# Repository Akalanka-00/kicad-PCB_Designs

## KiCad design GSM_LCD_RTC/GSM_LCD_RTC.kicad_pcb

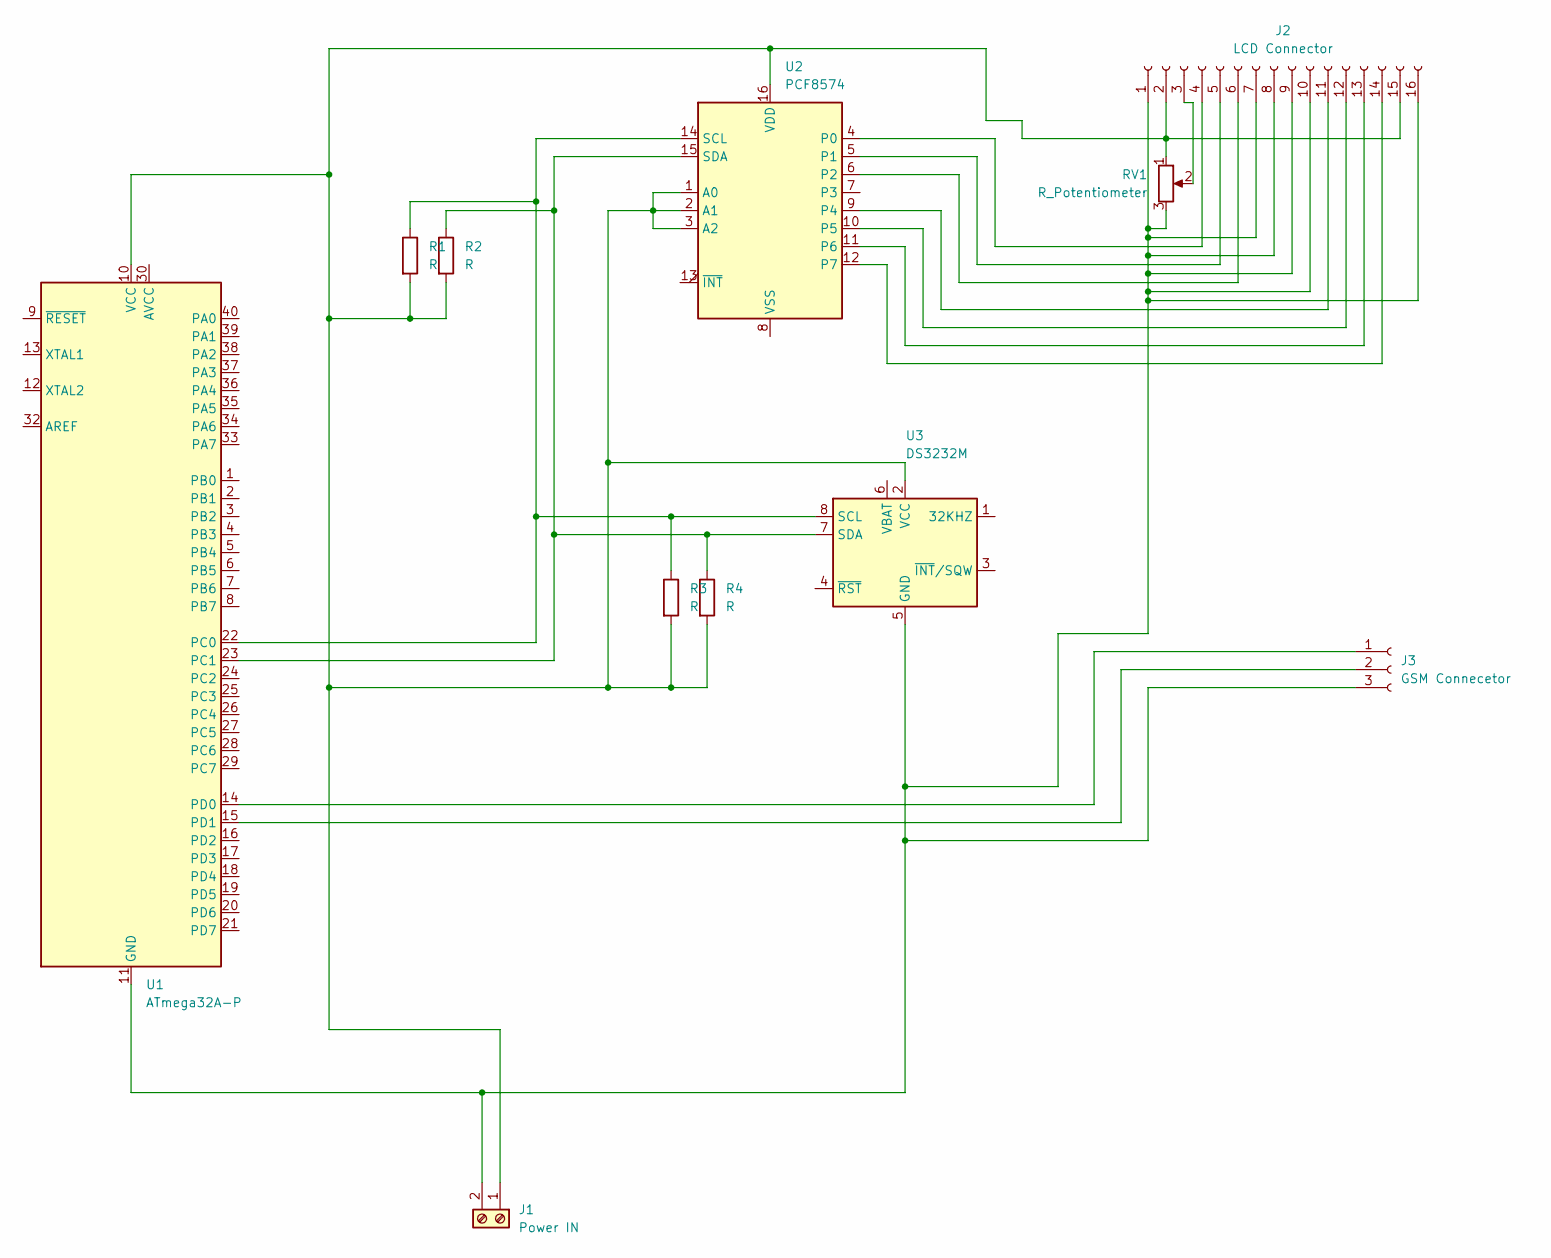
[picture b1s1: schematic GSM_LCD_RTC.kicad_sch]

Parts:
J1: Power IN; PhoenixContact_MSTBA_2,5_2-G_1x02_P5.00mm_Horizontal
J2: LCD Connector; PinHeader_1x16_P2.54mm_Vertical
J3: GSM Connecetor; PinSocket_1x03_P2.54mm_Vertical
R1, R2, R3, R4: R; R_Axial_DIN0411_L9.9mm_D3.6mm_P20.32mm_Horizontal
RV1: R_Potentiometer
U1: ATmega32A-P; DIP-40_W15.24mm
U2: PCF8574; Pololu_Breakout-16_15.2x20.3mm
U3: DS3232M; SOIC-8_3.9x4.9mm_P1.27mm

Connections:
unnamed: J1.1, J2.2, J2.15, R1.2, R2.2, R3.2, R4.2, RV1.1, U1.10 (VCC), U2.1 (A0), U2.2 (A1), U2.3 (A2), U2.16 (VDD), U3.2 (VCC)
unnamed: J1.2, J2.1, J2.7, J2.8, J2.9, J2.10, J2.16, J3.3, RV1.3, U1.11 (GND), U1.31 (GND), U3.5 (GND)
unnamed: J2.3, RV1.2
unnamed: J2.4, U2.4 (P0)
unnamed: J2.5, U2.5 (P1)
unnamed: J2.6, U2.6 (P2)
unnamed: J2.11, U2.9 (P4)
unnamed: J2.12, U2.10 (P5)
unnamed: J2.13, U2.11 (P6)
unnamed: J2.14, U2.12 (P7)
unnamed: J3.1, U1.14 (PD0)
unnamed: J3.2, U1.15 (PD1)
unnamed: R1.1, R3.1, U1.22 (PC0), U2.14 (SCL), U3.8 (SCL)
unnamed: R2.1, R4.1, U1.23 (PC1), U2.15 (SDA), U3.7 (SDA)

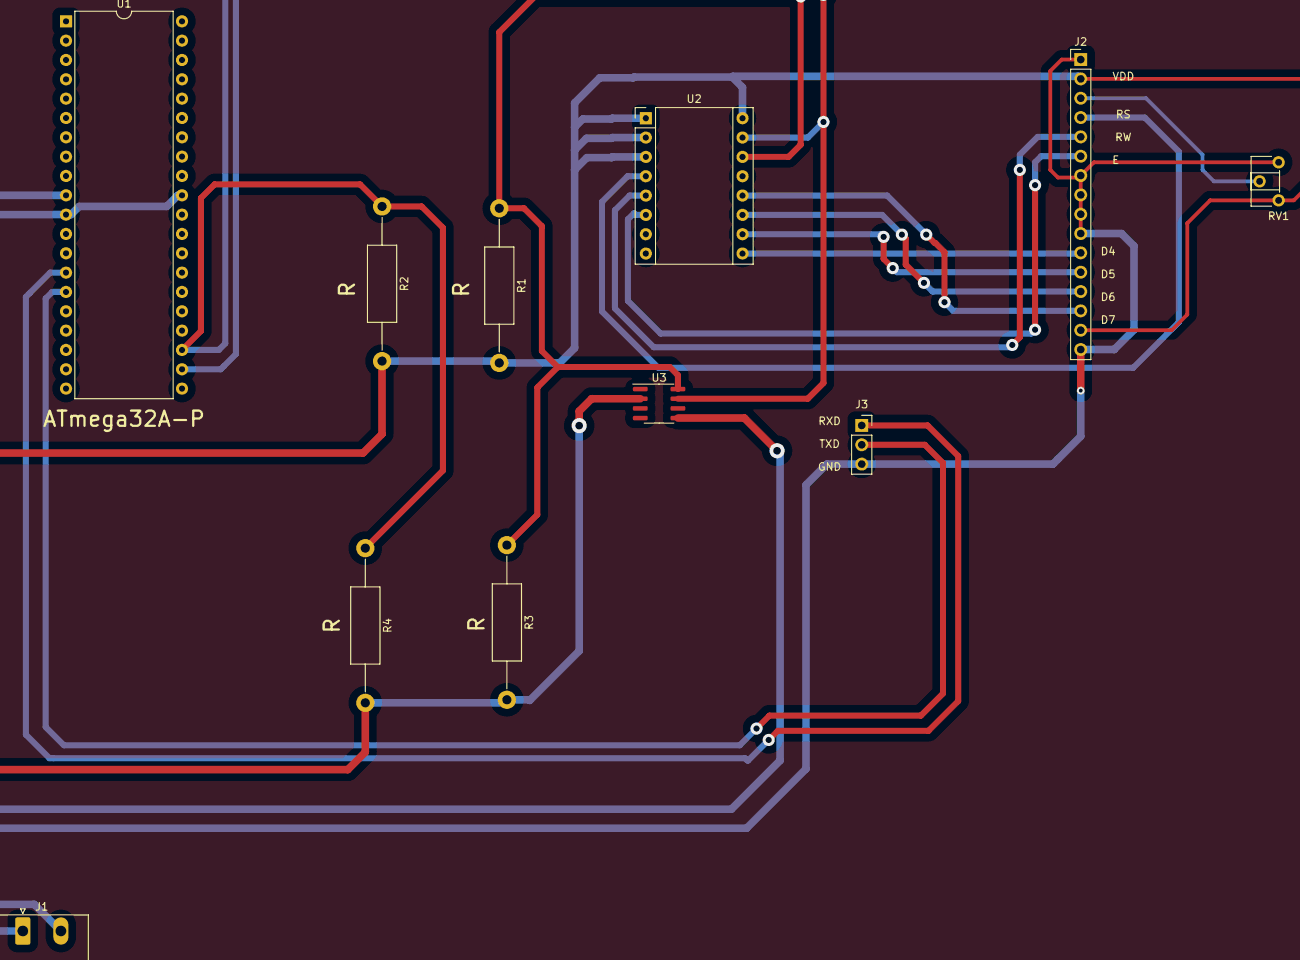
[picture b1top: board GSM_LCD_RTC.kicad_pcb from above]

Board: 2 copper layers, 11 parts (0 on the bottom side), 14 nets.

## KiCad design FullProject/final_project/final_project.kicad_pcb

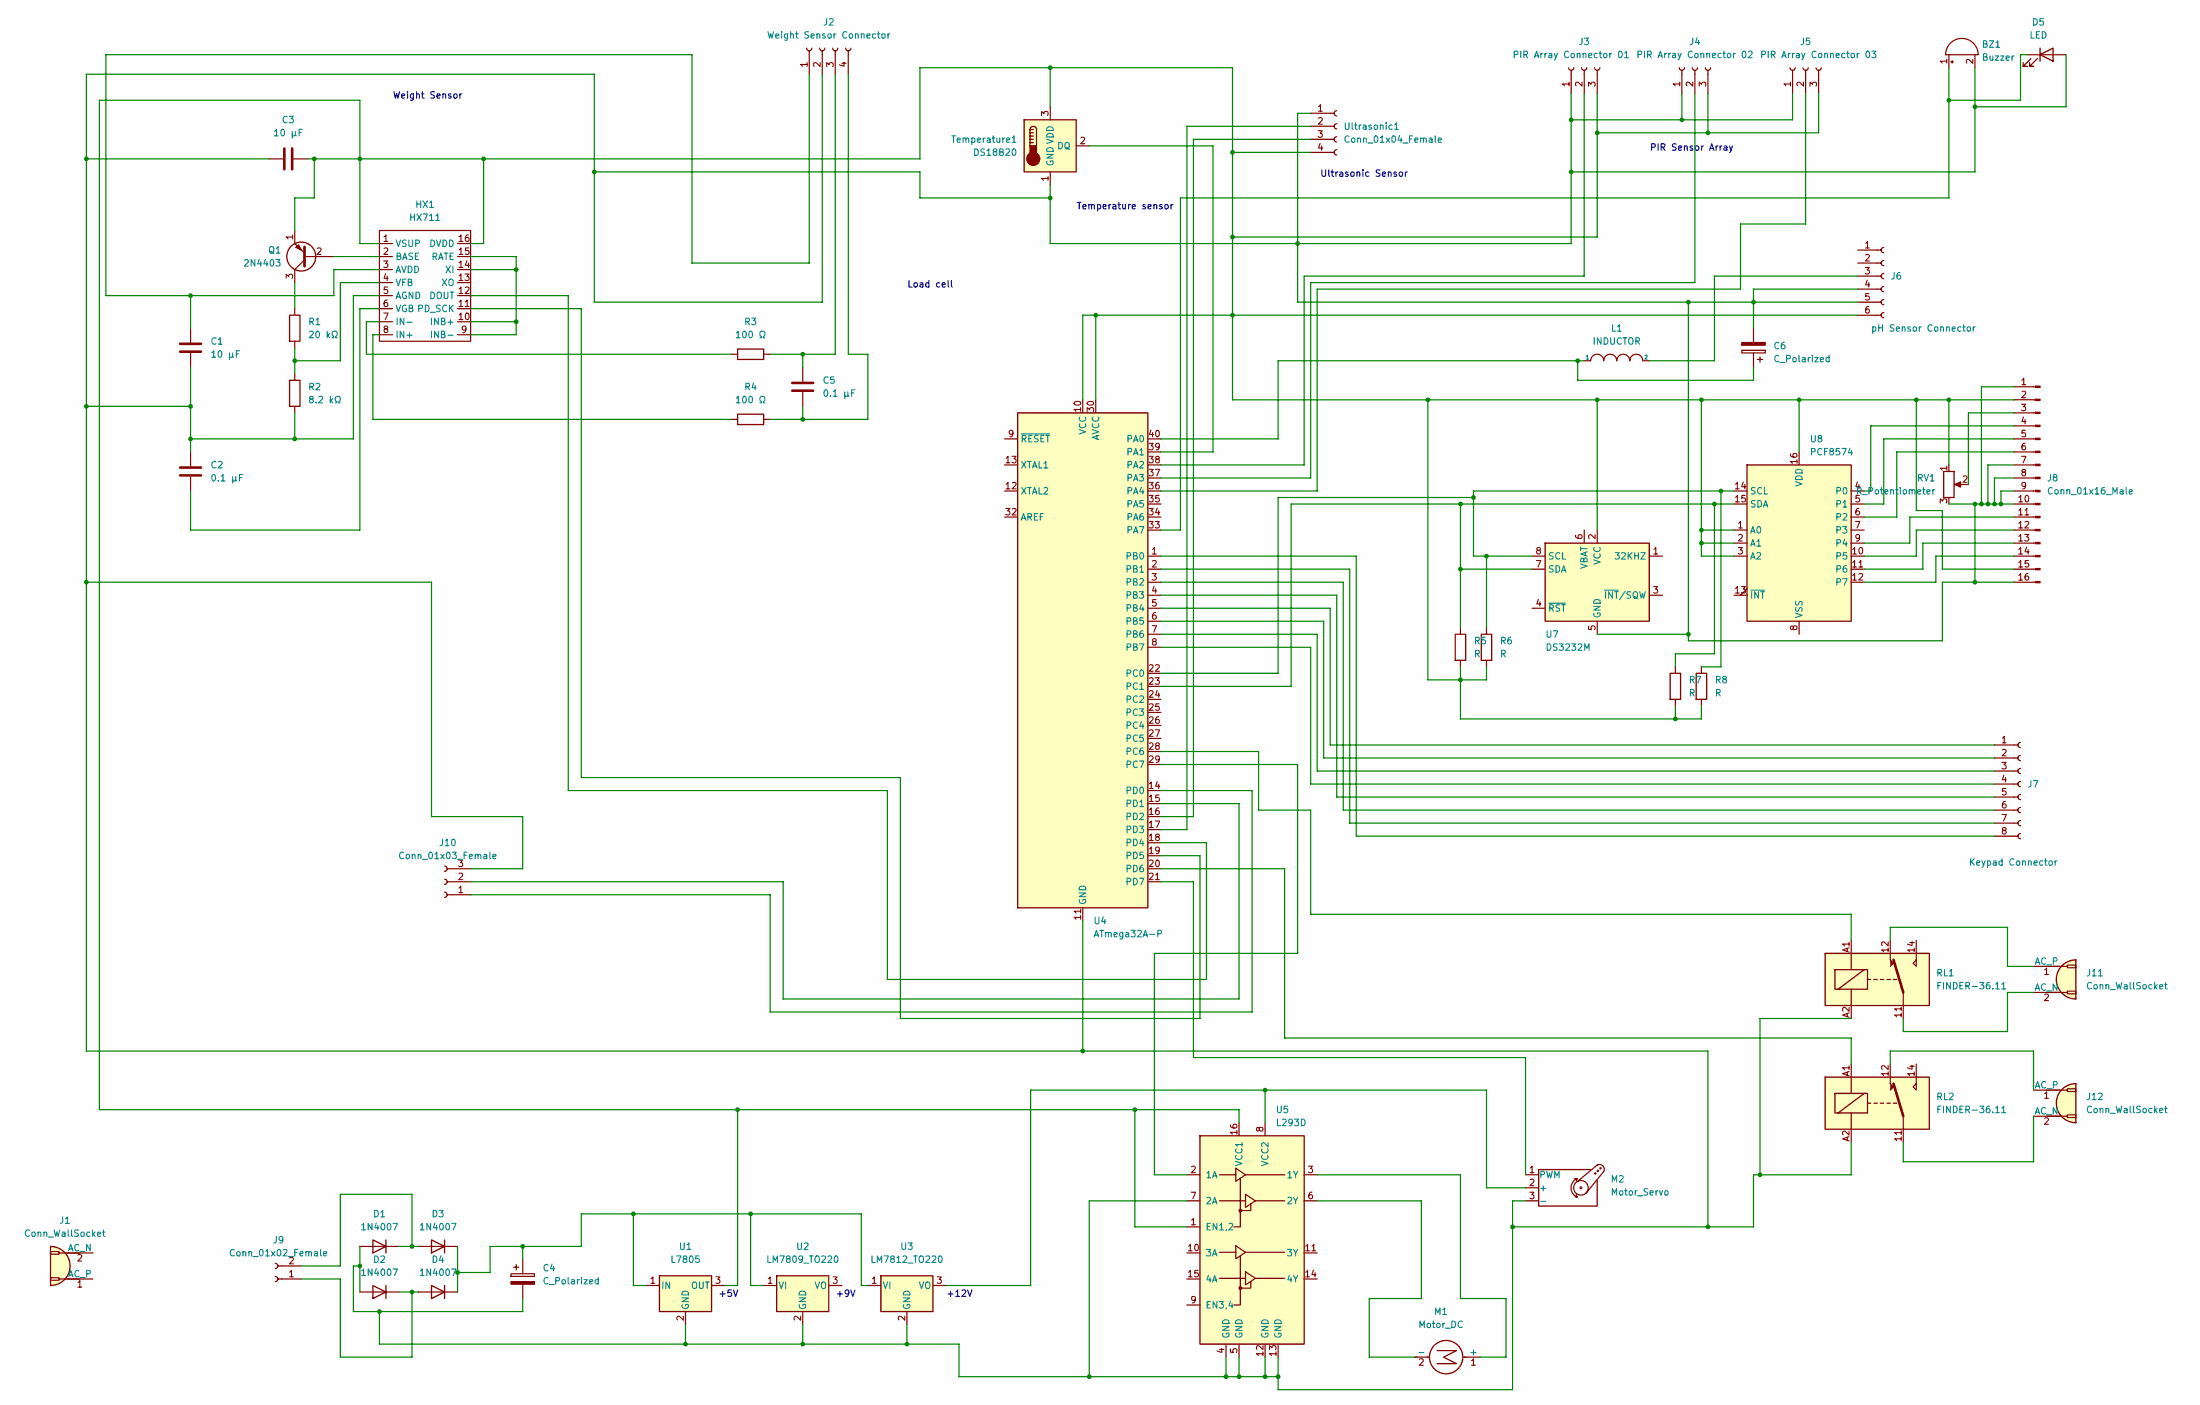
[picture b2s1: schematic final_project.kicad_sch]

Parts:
BZ1: Buzzer; Buzzer_15x7.5RM7.6
C1, C3: 10 μF; CP_Axial_L10.0mm_D4.5mm_P15.00mm_Horizontal
C2: 0.1 μF; CP_Axial_L10.0mm_D4.5mm_P15.00mm_Horizontal
C4: C_Polarized; CP_Axial_L11.0mm_D6.0mm_P18.00mm_Horizontal
C5: 0.1 μF; CP_Axial_L11.0mm_D5.0mm_P18.00mm_Horizontal
C6: C_Polarized; CP_Axial_L18.0mm_D8.0mm_P25.00mm_Horizontal
D1, D2, D3, D4: 1N4007; D_DO-41_SOD81_P10.16mm_Horizontal
D5: LED; LED_D3.0mm
HX1: HX711
J1, J11, J12: Conn_WallSocket; AMASS_XT60-M_1x02_P7.20mm_Vertical
J2: Weight Sensor Connector; PinSocket_1x04_P2.54mm_Vertical
J3: PIR Array Connector 01; PinSocket_1x03_P2.54mm_Vertical
J4: PIR Array Connector 02; PinSocket_1x03_P2.54mm_Vertical
J5: PIR Array Connector 03; PinSocket_1x03_P2.54mm_Vertical
J6: pH Sensor Connector; PinSocket_1x06_P2.54mm_Vertical
J7: Keypad Connector; PinSocket_1x08_P2.54mm_Horizontal
J8: Conn_01x16_Male; PinHeader_1x16_P2.54mm_Vertical
J9: Conn_01x02_Female; PhoenixContact_MSTBA_2,5_2-G_1x02_P5.00mm_Horizontal
J10: Conn_01x03_Female; PinSocket_1x03_P2.54mm_Vertical
L1: INDUCTOR; L_Axial_L9.5mm_D4.0mm_P12.70mm_Horizontal_Fastron_SMCC
M1: Motor_DC; TerminalBlock_Dinkle_DT-55-B01X-02_P10.00mm
M2: Motor_Servo; Stocko_MKS_1653-6-0-303_1x3_P2.50mm_Vertical
Q1: 2N4403; TO-92_Inline
R1: 20 kΩ; R_Axial_DIN0204_L3.6mm_D1.6mm_P5.08mm_Vertical
R2: 8.2 kΩ; R_Axial_DIN0204_L3.6mm_D1.6mm_P5.08mm_Vertical
R3, R4: 100 Ω; R_Axial_DIN0204_L3.6mm_D1.6mm_P5.08mm_Vertical
R5, R6, R7, R8: R; R_Axial_DIN0207_L6.3mm_D2.5mm_P7.62mm_Horizontal
RL1, RL2: FINDER-36.11; Relay_SPDT_Finder_36.11
RV1: R_Potentiometer; Potentiometer_ACP_CA6-H2,5_Horizontal
Temperature1: DS18B20; PinSocket_1x03_P2.54mm_Vertical
U1: L7805; TO-220-3_Vertical
U2: LM7809_TO220; TO-220-3_Vertical
U3: LM7812_TO220; TO-220-3_Vertical
U4: ATmega32A-P; DIP-40_W15.24mm
U5: L293D; DIP-16_W7.62mm
U7: DS3232M; SOIC-8_3.9x4.9mm_P1.27mm
U8: PCF8574; Pololu_Breakout-16_15.2x20.3mm
Ultrasonic1: Conn_01x04_Female; PinSocket_1x04_P2.54mm_Vertical

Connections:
unnamed: BZ1.1 (-), D5.1 (K), U4.33 (PA7)
unnamed: BZ1.2 (+), C1.2, C2.1, C3.2, C4.2, C6.2, D1.2 (A), D2.2 (A), D5.2 (A), HX1.5 (AGND), J2.2, J3.1, J4.1, J5.1, J6.4, J6.5, J8.1, J8.7, J8.8, J8.9, J8.10, J8.16, J10.3, M2.3 (-), R2.2, RL1.A2, RL2.A2, RV1.3, Temperature1.1 (GND), U1.2 (GND), U2.2 (GND), U3.2 (GND), U4.11 (GND), U4.31 (GND), U5.4 (GND), U5.5 (GND), U5.7 (2A), U5.12 (GND), U5.13 (GND), U7.5 (GND), Ultrasonic1.1
unnamed: C1.1, HX1.3 (AVDD), J2.1
unnamed: C2.2, HX1.6 (VGB)
unnamed: C3.1, HX1.1 (VSUP), HX1.16 (DVDD), J3.3, J4.3, J5.3, J6.6, J8.2, J8.15, Q1.1 (E), R5.2, R6.2, R7.2, R8.2, RV1.1, Temperature1.3 (VDD), U1.3 (OUT), U4.10 (VCC), U4.30 (AVCC), U5.1 (EN1,2), U5.16 (VCC1), U7.2 (VCC), U8.1 (A0), U8.2 (A1), U8.3 (A2), U8.16 (VDD), Ultrasonic1.4
unnamed: C4.1, D3.1 (K), D4.1 (K), U1.1 (IN), U2.1 (VI), U3.1 (VI)
unnamed: C5.1, J2.3, R3.2
unnamed: C5.2, J2.4, R4.2
unnamed: C6.1, L1.1, U4.40 (PA0)
unnamed: D1.1 (K), D3.2 (A), J9.2
unnamed: D2.1 (K), D4.2 (A), J9.1
unnamed: HX1.2 (BASE), Q1.2 (B)
unnamed: HX1.4 (VFB), R1.2, R2.1
unnamed: HX1.7 (IN-), R3.1
unnamed: HX1.8 (IN+), R4.1
unnamed: HX1.9 (INB-), HX1.10 (INB+), HX1.14 (XI), HX1.15 (RATE)
unnamed: HX1.11 (PD_SCK), U4.19 (PD5)
unnamed: HX1.12 (DOUT), U4.18 (PD4)
unnamed: J3.2, U4.38 (PA2)
unnamed: J4.2, U4.37 (PA3)
unnamed: J5.2, U4.36 (PA4)
unnamed: J6.3, L1.2
unnamed: J7.1, U4.5 (PB4)
unnamed: J7.2, U4.6 (PB5)
unnamed: J7.3, U4.7 (PB6)
unnamed: J7.4, U4.8 (PB7)
unnamed: J7.5, U4.4 (PB3)
unnamed: J7.6, U4.3 (PB2)
unnamed: J7.7, U4.2 (PB1)
unnamed: J7.8, U4.1 (PB0)
unnamed: J8.3, RV1.2
unnamed: J10.1, U4.14 (PD0)
unnamed: J10.2, U4.15 (PD1)
unnamed: J11.1 (AC_P), RL1.12
unnamed: J11.2 (AC_N), RL1.11
unnamed: J12.1 (AC_P), RL2.12
unnamed: J12.2 (AC_N), RL2.11
unnamed: M1.1 (+), U5.3 (1Y)
unnamed: M1.2 (-), U5.6 (2Y)
unnamed: M2.1 (PWM), U4.21 (PD7)
unnamed: M2.2 (+), U3.3 (VO), U5.8 (VCC2)
unnamed: Q1.3 (C), R1.1
unnamed: R5.1, R7.1, U4.23 (PC1), U7.7 (SDA), U8.15 (SDA)
unnamed: R6.1, R8.1, U4.22 (PC0), U7.8 (SCL), U8.14 (SCL)
unnamed: RL1.A1, U4.28 (PC6)
unnamed: RL2.A1, U4.20 (PD6)
unnamed: Temperature1.2 (DQ), U4.39 (PA1)
unnamed: U4.16 (PD2), Ultrasonic1.3
unnamed: U4.17 (PD3), Ultrasonic1.2
unnamed: U4.29 (PC7), U5.2 (1A)
unnamed: J8.4, U8.4 (P0)
unnamed: J8.5, U8.5 (P1)
unnamed: J8.6, U8.6 (P2)
unnamed: J8.11, U8.9 (P4)
unnamed: J8.12, U8.10 (P5)
unnamed: J8.13, U8.11 (P6)
unnamed: J8.14, U8.12 (P7)

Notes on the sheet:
+5V
+12V
Load cell
Temperature sensor
Weight Sensor
Ultrasonic Sensor
PIR Sensor Array
+9V

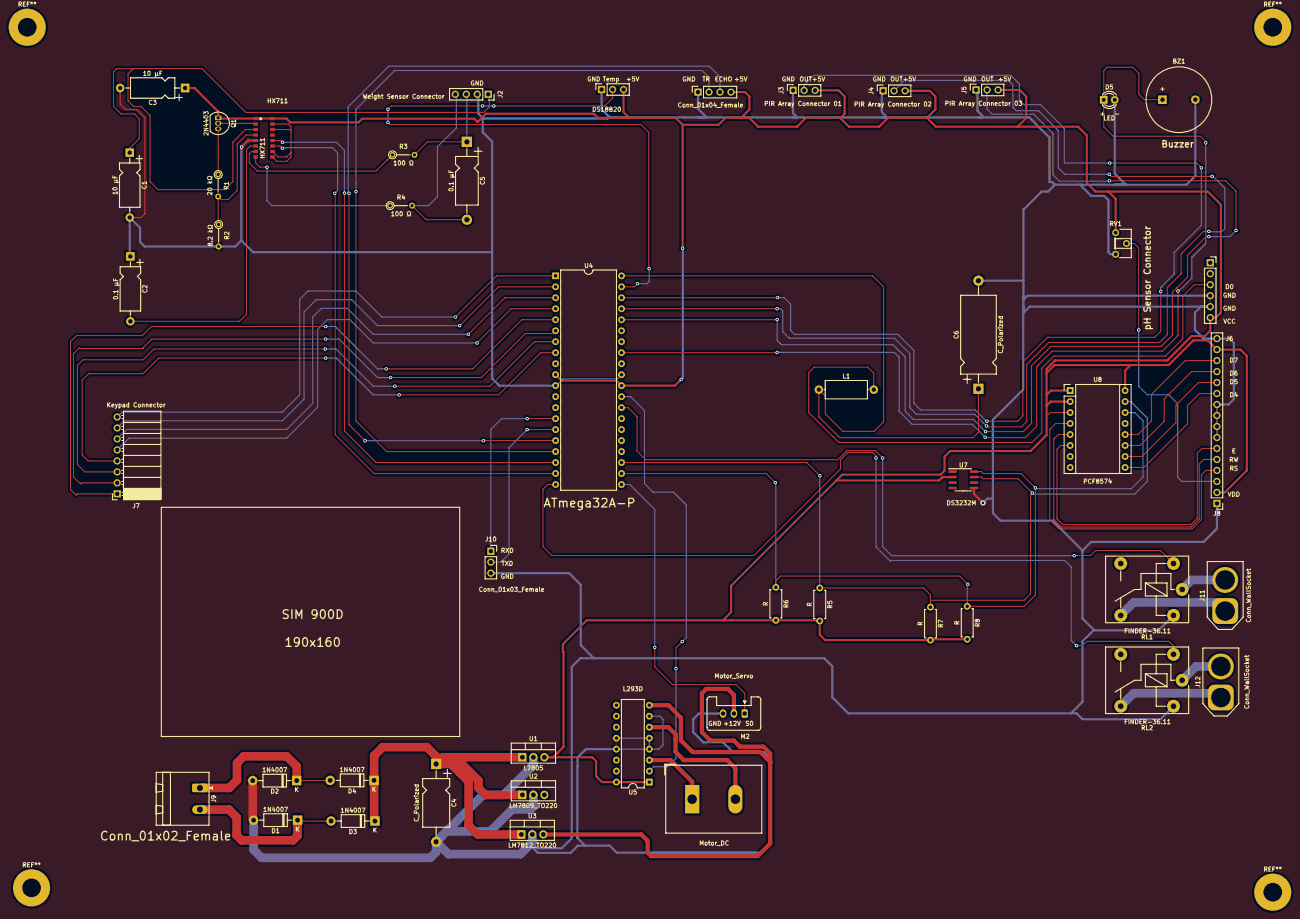
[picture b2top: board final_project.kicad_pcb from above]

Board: 2 copper layers, 48 parts (0 on the bottom side), 57 nets.

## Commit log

2022-06-09 hx711
